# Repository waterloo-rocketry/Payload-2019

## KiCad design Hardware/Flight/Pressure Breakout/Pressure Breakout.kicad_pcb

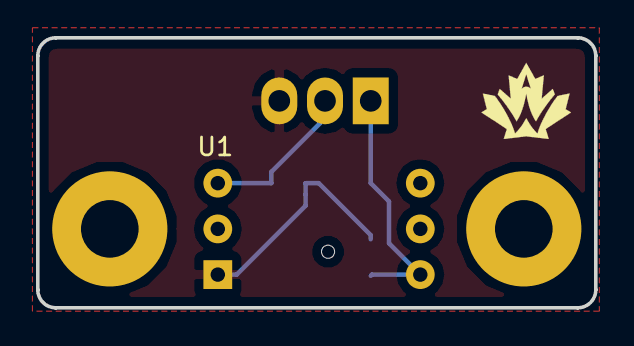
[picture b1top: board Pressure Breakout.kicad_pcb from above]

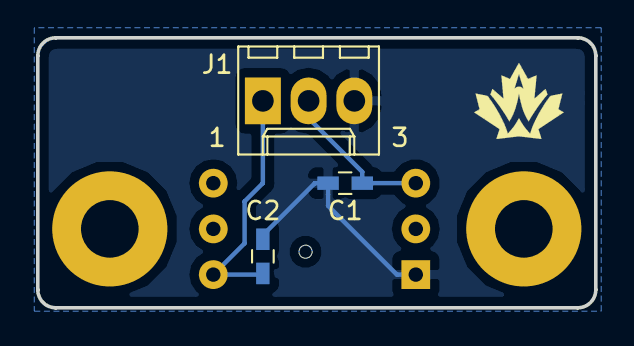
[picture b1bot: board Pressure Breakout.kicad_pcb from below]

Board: 2 copper layers, 31.0 x 15.0 mm, 4 parts (3 on the bottom side), 3 nets.

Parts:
C1: 0.001uF; C_0603_HandSoldering
C2: 0.1uF; C_0603_HandSoldering
J1: Conn_01x03; Molex_KK-6410-03_03x2.54mm_Straight
U1: ABPDANT005PGAA5; DIP-6_W11.25mm

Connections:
+5V: C2.1, J1.1, U1.6
/VOUT: C1.1, J1.2, U1.3
GND: C1.2, C2.2, J1.3, U1.1

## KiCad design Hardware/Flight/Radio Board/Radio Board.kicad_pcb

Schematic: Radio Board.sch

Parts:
C1, C2: 10uF; C_0603_HandSoldering
D1, D2, D3, D4: LED; LED_0603_HandSoldering
J1: Bus_Connector; Pin_Header_Straight_2x10_Pitch2.54mm
J2, J3: Conn_Coaxial; U.FL_Hirose_U.FL-R-SMT-1_Vertical
R1, R2: 10k; R_0603_HandSoldering
R3, R4: DNP; R_0603_HandSoldering
R5, R6, R7, R8: 70; R_0603_HandSoldering
U1, U2: RFM95W-915S2; Hopref_RFM9XW_SMD

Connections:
+3V3: C1.1, C2.1, J1.19, R1.1, R2.1, R3.1, R4.1, U1.13 (3.3V), U2.13 (3.3V)
/INT1: J1.5, R5.2, U1.14 (DIO0)
/INT2: J1.4, R6.2, U2.14 (DIO0)
/MISO: J1.6, U1.2 (MISO), U2.2 (MISO)
/MOSI: J1.7, U1.3 (MOSI), U2.3 (MOSI)
/SCK: J1.8, U1.4 (SCK), U2.4 (SCK)
/~CS1: J1.9, R3.2, U1.5 (NSS)
/~CS2: J1.10, R4.2, U2.5 (NSS)
GND: C1.2, C2.2, D1.1, D2.1, D3.1, D4.1, J1.1, J2.2, J3.2, U1.1 (GND), U1.8 (GND), U1.10 (GND), U2.1 (GND), U2.8 (GND), U2.10 (GND)
unnamed: D1.2, R5.1
unnamed: D2.2, R6.1
unnamed: D3.2, R7.1
unnamed: D4.2, R8.1
unnamed: J2.1, U1.9 (ANT)
unnamed: J3.1, U2.9 (ANT)
unnamed: R1.2, U1.6 (RESET)
unnamed: R2.2, U2.6 (RESET)
unnamed: R7.2, U1.11 (DIO3)
unnamed: R8.2, U2.11 (DIO3)

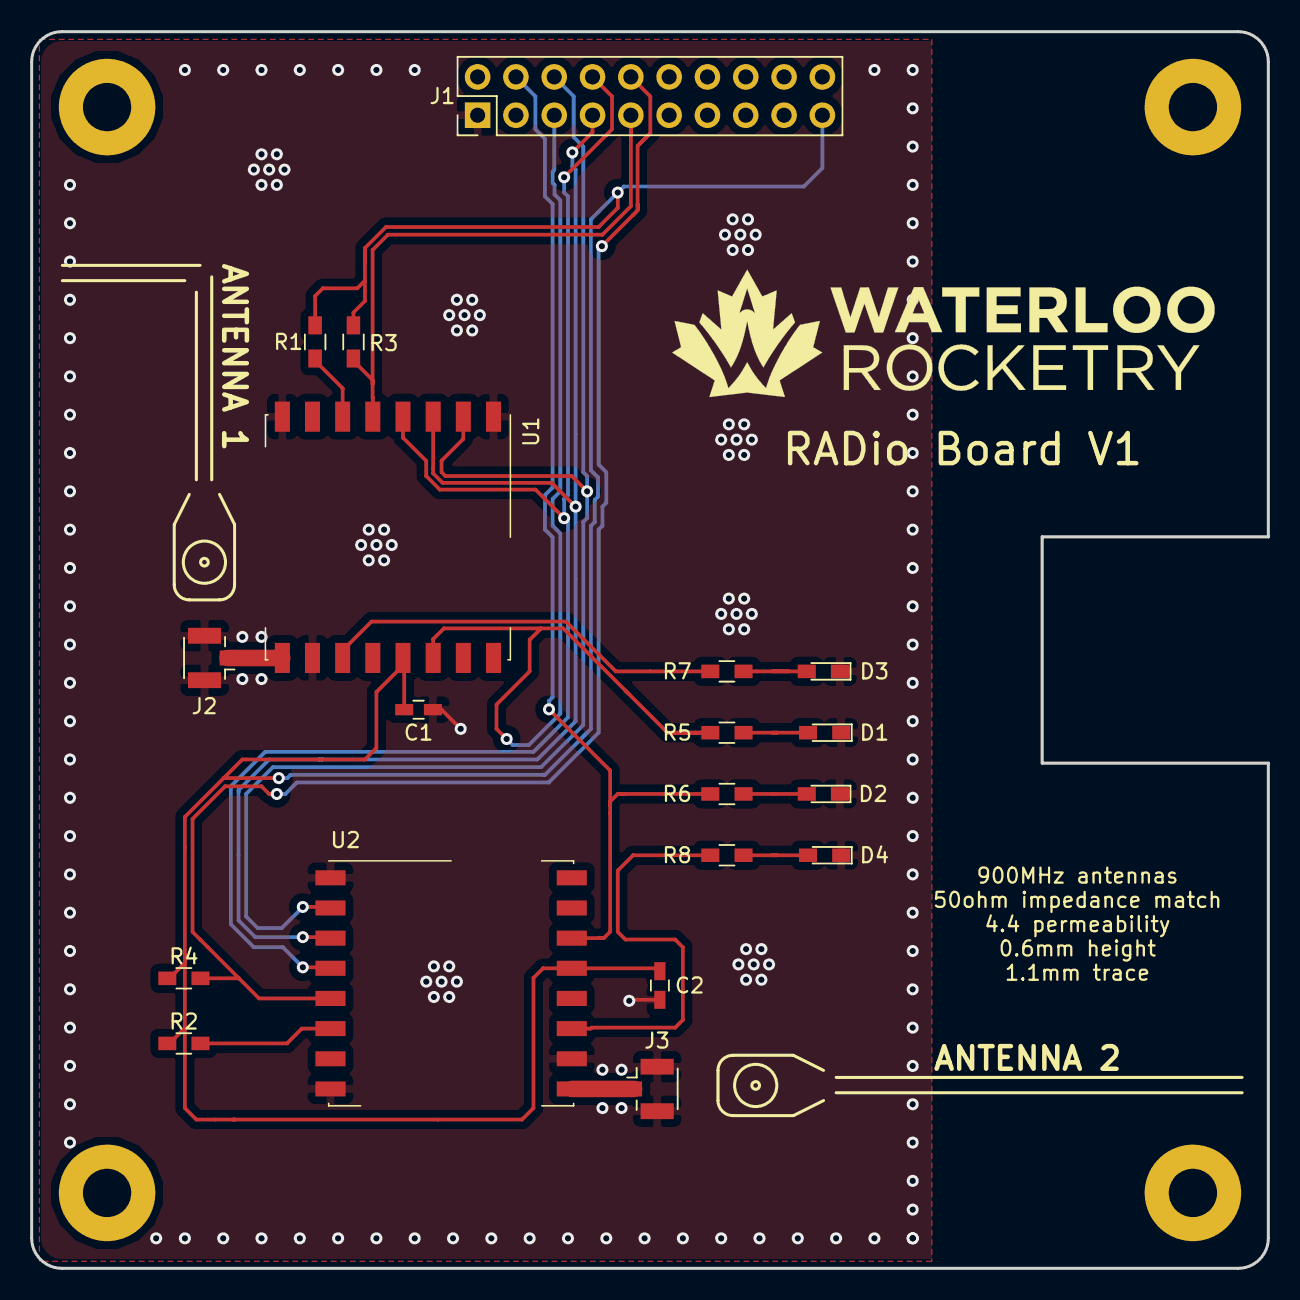
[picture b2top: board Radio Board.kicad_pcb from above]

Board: 2 copper layers, 82.0 x 82.0 mm, 19 parts (0 on the bottom side), 19 nets.

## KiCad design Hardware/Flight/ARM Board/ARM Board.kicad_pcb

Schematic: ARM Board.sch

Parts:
C1, C2: 47pF; C_0603_HandSoldering
C3: .01uF; C_0603_HandSoldering
C4, C5, C6, C22: 0.1uF; C_0603_HandSoldering
C7: 4.7uF; C_0603_HandSoldering
D1: D_TVS; D_0603
J1: Bus_Connector; Pin_Header_Straight_2x10_Pitch2.54mm
J2: USB_B_Micro; 10118194-0001LF
J3: Harwin_M80-5400642; connector_Harwin_M80-5000642
J4, J5: SD_Card; SD_Card_Receptacle
JP1, JP2, JP3, JP4, JP5, JP6, JP7, JP8, JP9, JP10, JP11, JP12, JP13, JP14, JP15, JP16, JP17, JP18, JP21, JP22, JP23, JP24, JP25, JP26, JP27, JP28, JP29, JP30: Jumper; SolderJumper-2_P1.3mm_Open_RoundedPad1.0x1.5mm
R1: DNP; R_0603_HandSoldering
R2, R3: 27; R_0603_HandSoldering
R4: R; R_0603_HandSoldering
U1: MCP2562-canhw; SOIC-8_3.9x4.9mm_Pitch1.27mm
U2: FT231XS; SSOP-20_3.9x8.7mm_P0.635mm
U6: MCP9700AT-ETT; SOT-23_Handsoldering

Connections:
+3V3: C6.1, C7.1, C22.1, J4.1, J4.4, J5.4, JP14.2, R4.1, U1.5, U6.1 (Vdd); also elsewhere on the board
+5V: C5.1, U1.3; also elsewhere on the board
/3V3_BUS: J1.19; also elsewhere on the board
/5_BUS: J1.20; also elsewhere on the board
/5_USB: C3.1, D1.1, J2.1, U2.15; also elsewhere on the board
/ARM&RAMMER/CANRX: JP9.1; also elsewhere on the board
/ARM&RAMMER/CANTX: JP8.2; also elsewhere on the board
/ARM&RAMMER/CARD_DETECT_1: J5.10; also elsewhere on the board
/ARM&RAMMER/CARD_DETECT_2: J4.10; also elsewhere on the board
/ARM&RAMMER/MISO1: JP17.1; also elsewhere on the board
/ARM&RAMMER/MISO2: JP5.2; also elsewhere on the board
/ARM&RAMMER/MOSI1: JP15.1; also elsewhere on the board
/ARM&RAMMER/MOSI2: JP4.2; also elsewhere on the board
/ARM&RAMMER/RADIO_INT_1: JP21.2; also elsewhere on the board
/ARM&RAMMER/RADIO_INT_2: JP22.2; also elsewhere on the board
/ARM&RAMMER/RES0: JP25.2; also elsewhere on the board
/ARM&RAMMER/RES1: JP26.2; also elsewhere on the board
/ARM&RAMMER/RES2: JP27.2; also elsewhere on the board
/ARM&RAMMER/RES3: JP28.2; also elsewhere on the board
/ARM&RAMMER/SCK1: JP16.1; also elsewhere on the board
/ARM&RAMMER/SCK2: JP3.2; also elsewhere on the board
/ARM&RAMMER/SCL: JP6.2; also elsewhere on the board
/ARM&RAMMER/SDA: JP7.2; also elsewhere on the board
/ARM&RAMMER/TEMP: U6.2 (Vout); also elsewhere on the board
/ARM&RAMMER/UART_RX: JP10.2, JP23.2; also elsewhere on the board
/ARM&RAMMER/UART_TX: JP11.2, JP24.2; also elsewhere on the board
/ARM&RAMMER/UART_~CTS: JP13.2; also elsewhere on the board
/ARM&RAMMER/UART_~RTS: JP12.2; also elsewhere on the board
/ARM&RAMMER/~CAN_EN: U1.8; also elsewhere on the board
/ARM&RAMMER/~CS1: JP14.1; also elsewhere on the board
/ARM&RAMMER/~CS1_2: JP18.1; also elsewhere on the board
/ARM&RAMMER/~CS2: JP2.2; also elsewhere on the board
/ARM&RAMMER/~CS2_2: JP1.2; also elsewhere on the board
/ARM&RAMMER/~FAULT1: JP29.2; also elsewhere on the board
/ARM&RAMMER/~FAULT2: JP30.2; also elsewhere on the board
/CAN-SENSE/VIN: J3.2; also elsewhere on the board
/D2+: R2.1, U2.11
/D2-: R3.1, U2.12
/D+: C1.1, J2.3, R2.2
/D-: C2.1, J2.2, R3.2
GND: C1.2, C2.2, C3.2, C4.2, C5.2, C6.2, C7.2, C22.2, D1.2, J1.1, J2.5, J3.3, J4.3, J4.6, J4.12, J4.13, J5.3, J5.6, J5.12, J5.13, U1.2, U2.6, U2.16, U6.3 (GND); also elsewhere on the board
unnamed: C4.1, U2.3, U2.13, U2.14
unnamed: J1.2, JP7.1
unnamed: J1.3, JP6.1
unnamed: J1.4, JP22.1
unnamed: J1.5, JP21.1
unnamed: J1.6, JP5.1
unnamed: J1.7, JP4.1
unnamed: J1.8, JP3.1
unnamed: J1.9, JP2.1
unnamed: J1.10, JP1.1
unnamed: J1.11, JP30.1
unnamed: J1.12, JP29.1
unnamed: J1.13, JP28.1
unnamed: J1.14, JP27.1
unnamed: J1.15, JP26.1
unnamed: J1.16, JP25.1
unnamed: J1.17, JP24.1
unnamed: J1.18, JP23.1
unnamed: J3.4, R1.1, U1.7
unnamed: J3.5, R1.2, U1.6
unnamed: J4.2, J5.2, JP15.2
unnamed: J4.5, J5.5, JP16.2
unnamed: J4.7, J5.7, JP17.2, R4.2
unnamed: J5.1, JP18.2
unnamed: JP8.1, U1.1
unnamed: JP9.2, U1.4
unnamed: JP10.1, U2.20
unnamed: JP11.1, U2.4
unnamed: JP12.1, U2.2
unnamed: JP13.1, U2.9

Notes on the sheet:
SD Card Logging
USB POWER + PROGRAMMING
CUBESAT BUS CONNECTOR
CAN LOGIC
POWER MANAGEMENT
ONLY POWERED WHEN USB CONNECTED
CANHW CURRENT SENSING

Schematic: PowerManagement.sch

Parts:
C8, C9: 10uF; C_0603_HandSoldering
D2, D3, D5: D_Schottky_x2_KCom_AAK; SOT-23_Handsoldering
D4: BAT60JFILM; D_SOD-323_HandSoldering
JP19, JP20: Jumper; SolderJumper-2_P1.3mm_Open_RoundedPad1.0x1.5mm
Q1: Q_PMOS_GSD; SOT-23_Handsoldering
R5: 10k; R_0603_HandSoldering
VR1: LD39200PU33R; DFN-6-1EP_3x3mm_Pitch0.95mm

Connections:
+3V3: D5.3; also elsewhere on the board
+5V: C8.1, D3.3, JP20.1, VR1.5, VR1.6; also elsewhere on the board
/3V3_BUS: D5.1; also elsewhere on the board
/5_BUS: D2.2, D3.1; also elsewhere on the board
/5_CANHW: Q1.2; also elsewhere on the board
/5_USB: D2.1, D3.2; also elsewhere on the board
GND: C8.2, C9.2, R5.2, VR1.3; also elsewhere on the board
unnamed: C9.1, D5.2, VR1.1, VR1.2
unnamed: D2.3, JP19.1
unnamed: D4.1, Q1.3
unnamed: D4.2, JP20.2
unnamed: JP19.2, Q1.1, R5.1

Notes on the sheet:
3.3v source selection (batt board or local)
5v source selection (canhw, bus or usb)
selected 5v source to 3.3v

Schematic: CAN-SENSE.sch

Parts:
C21: C
D6: D_TVS
R9: 62m
U5: INA180

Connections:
+3V3: C21.2, U5.5; also elsewhere on the board
/5_CANHW: R9.1, U5.4; also elsewhere on the board
/ARM&RAMMER/CURR_AMP: U5.1; also elsewhere on the board
/CAN-SENSE/VIN: D6.1; also elsewhere on the board
GND: C21.1, D6.2, U5.2; also elsewhere on the board
unnamed 66: R9.2, U5.3; also elsewhere on the board

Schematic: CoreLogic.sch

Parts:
C10: 4.7uF; C_0603_HandSoldering
C11, C12, C13, C17: 100nF; C_0603_HandSoldering
C14, C15: 1uF; C_0603_HandSoldering
C16: 10uF; C_0603_HandSoldering
C18: 0.1uF; C_0603_HandSoldering
C19, C20: C_Small; C_0603_HandSoldering
D7, D8, D9: LED; LED_0603_HandSoldering
J6: Conn_01x10; Pin_Header_Straight_2x05_Pitch2.54mm
JP31: Jumper; SolderJumper-2_P1.3mm_Open_RoundedPad1.0x1.5mm
L1: Ferrite_Bead; R_0603_HandSoldering
R6, R8: 4.7K; R_0603_HandSoldering
R10, R11, R12: 70; R_0603_HandSoldering
U3: STM32L4x6RxT6-symbols; STM32L4x6RxT6
U4: SRAM_23LC1024T-I_ST-ARMlib; TSSOP-8_4.4x3mm_Pitch0.65mm
Y1: Crystal; Crystal_HC49-U_Vertical

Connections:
+3V3: C10.1, C11.1, C12.1, C13.1, D7.2, D8.2, D9.2, J6.1, J6.7, L1.2, R6.1, R8.1, U3.1, U3.19, U3.32, U3.48, U3.64, U4.7, U4.8; also elsewhere on the board
/ARM&RAMMER/CANRX: U3.44; also elsewhere on the board
/ARM&RAMMER/CANTX: U3.45; also elsewhere on the board
/ARM&RAMMER/CARD_DETECT_1: U3.26; also elsewhere on the board
/ARM&RAMMER/CARD_DETECT_2: U3.27; also elsewhere on the board
/ARM&RAMMER/CURR_AMP: U3.10; also elsewhere on the board
/ARM&RAMMER/JTCK_SWCLK: J6.4, U3.49
/ARM&RAMMER/JTDI: J6.8, U3.50
/ARM&RAMMER/JTDO_SWO: J6.6, U3.55
/ARM&RAMMER/JTMS_SWDIO: J6.2, U3.46
/ARM&RAMMER/MISO1: U3.22; also elsewhere on the board
/ARM&RAMMER/MISO2: U3.35; also elsewhere on the board
/ARM&RAMMER/MISO3: U3.52, U4.2
/ARM&RAMMER/MOSI1: U3.23; also elsewhere on the board
/ARM&RAMMER/MOSI2: U3.36; also elsewhere on the board
/ARM&RAMMER/MOSI3: U3.53, U4.5
/ARM&RAMMER/PH3-BOOT0: J6.9, U3.60
/ARM&RAMMER/RADIO_INT_1: U3.11; also elsewhere on the board
/ARM&RAMMER/RADIO_INT_2: U3.25; also elsewhere on the board
/ARM&RAMMER/RES0: U3.37; also elsewhere on the board
/ARM&RAMMER/RES1: U3.38; also elsewhere on the board
/ARM&RAMMER/RES2: U3.39; also elsewhere on the board
/ARM&RAMMER/RES3: U3.40; also elsewhere on the board
/ARM&RAMMER/SCK1: U3.21; also elsewhere on the board
/ARM&RAMMER/SCK2: U3.42; also elsewhere on the board
/ARM&RAMMER/SCK3: U3.51, U4.6
/ARM&RAMMER/SCL: R6.2, U3.8; also elsewhere on the board
/ARM&RAMMER/SDA: R8.2, U3.9; also elsewhere on the board
/ARM&RAMMER/TEMP: U3.28; also elsewhere on the board
/ARM&RAMMER/UART_RX: U3.17; also elsewhere on the board
/ARM&RAMMER/UART_TX: U3.16; also elsewhere on the board
/ARM&RAMMER/UART_~CTS: U3.14; also elsewhere on the board
/ARM&RAMMER/UART_~RTS: U3.15; also elsewhere on the board
/ARM&RAMMER/~(JTRST|RST): J6.10, JP31.1, U3.56
/ARM&RAMMER/~CAN_EN: U3.43; also elsewhere on the board
/ARM&RAMMER/~CS1: U3.20; also elsewhere on the board
/ARM&RAMMER/~CS1_2: U3.24; also elsewhere on the board
/ARM&RAMMER/~CS2: U3.41; also elsewhere on the board
/ARM&RAMMER/~CS2_2: U3.34; also elsewhere on the board
/ARM&RAMMER/~CS3: U3.58, U4.1
/ARM&RAMMER/~FAULT1: U3.2; also elsewhere on the board
/ARM&RAMMER/~FAULT2: U3.54; also elsewhere on the board
/ARM&RAMMER/~HOLD3: U3.57
GND: C10.2, C11.2, C12.2, C13.2, C14.2, C15.2, C16.2, C17.2, C18.2, C19.2, C20.2, J6.3, J6.5, U3.12, U3.18, U3.31, U3.47, U3.63, U4.3, U4.4; also elsewhere on the board
unnamed: C14.1, C15.1, C16.1, C17.1, L1.1, U3.13
unnamed: C18.1, JP31.2, U3.7
unnamed: C19.1, U3.3, Y1.1
unnamed: C20.1, U3.4, Y1.2
unnamed: D7.1, R10.1
unnamed: D8.1, R11.1
unnamed: D9.1, R12.1
unnamed: R10.2, U3.59
unnamed: R11.2, U3.61
unnamed: R12.2, U3.62

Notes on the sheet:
RAM
STM PROGRAMMING HEADER
STM POWER MANAGEMENT
STM LOGIC
2v drop, 20mA max per pin

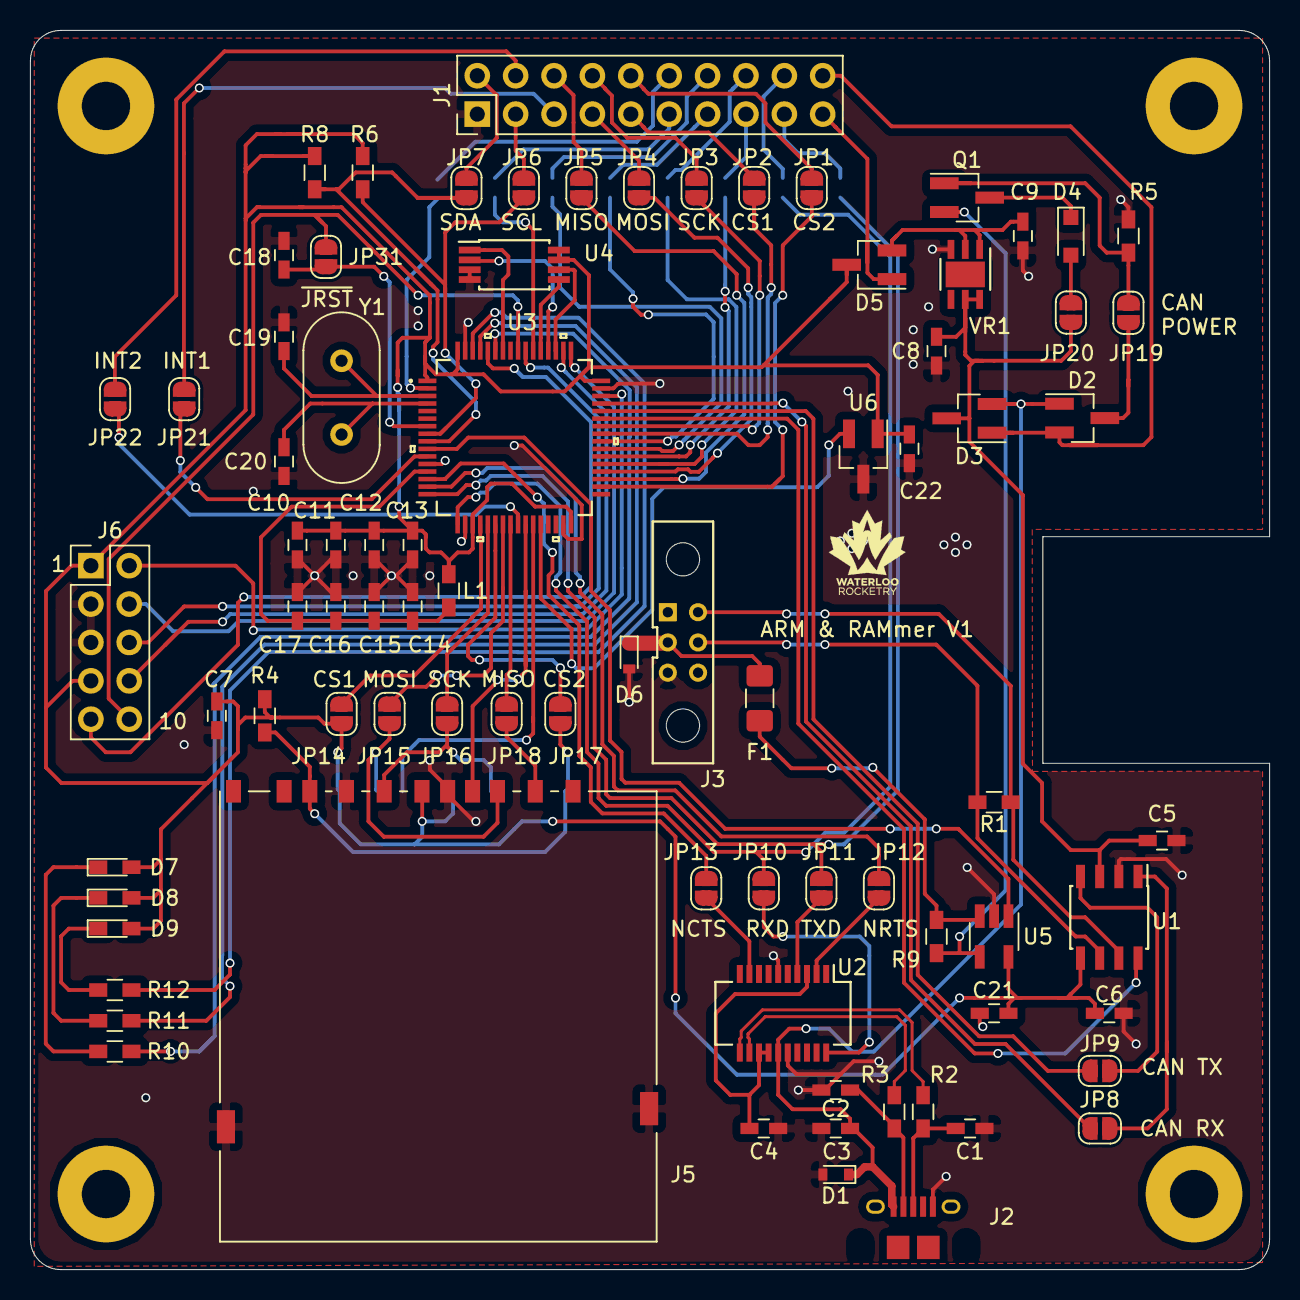
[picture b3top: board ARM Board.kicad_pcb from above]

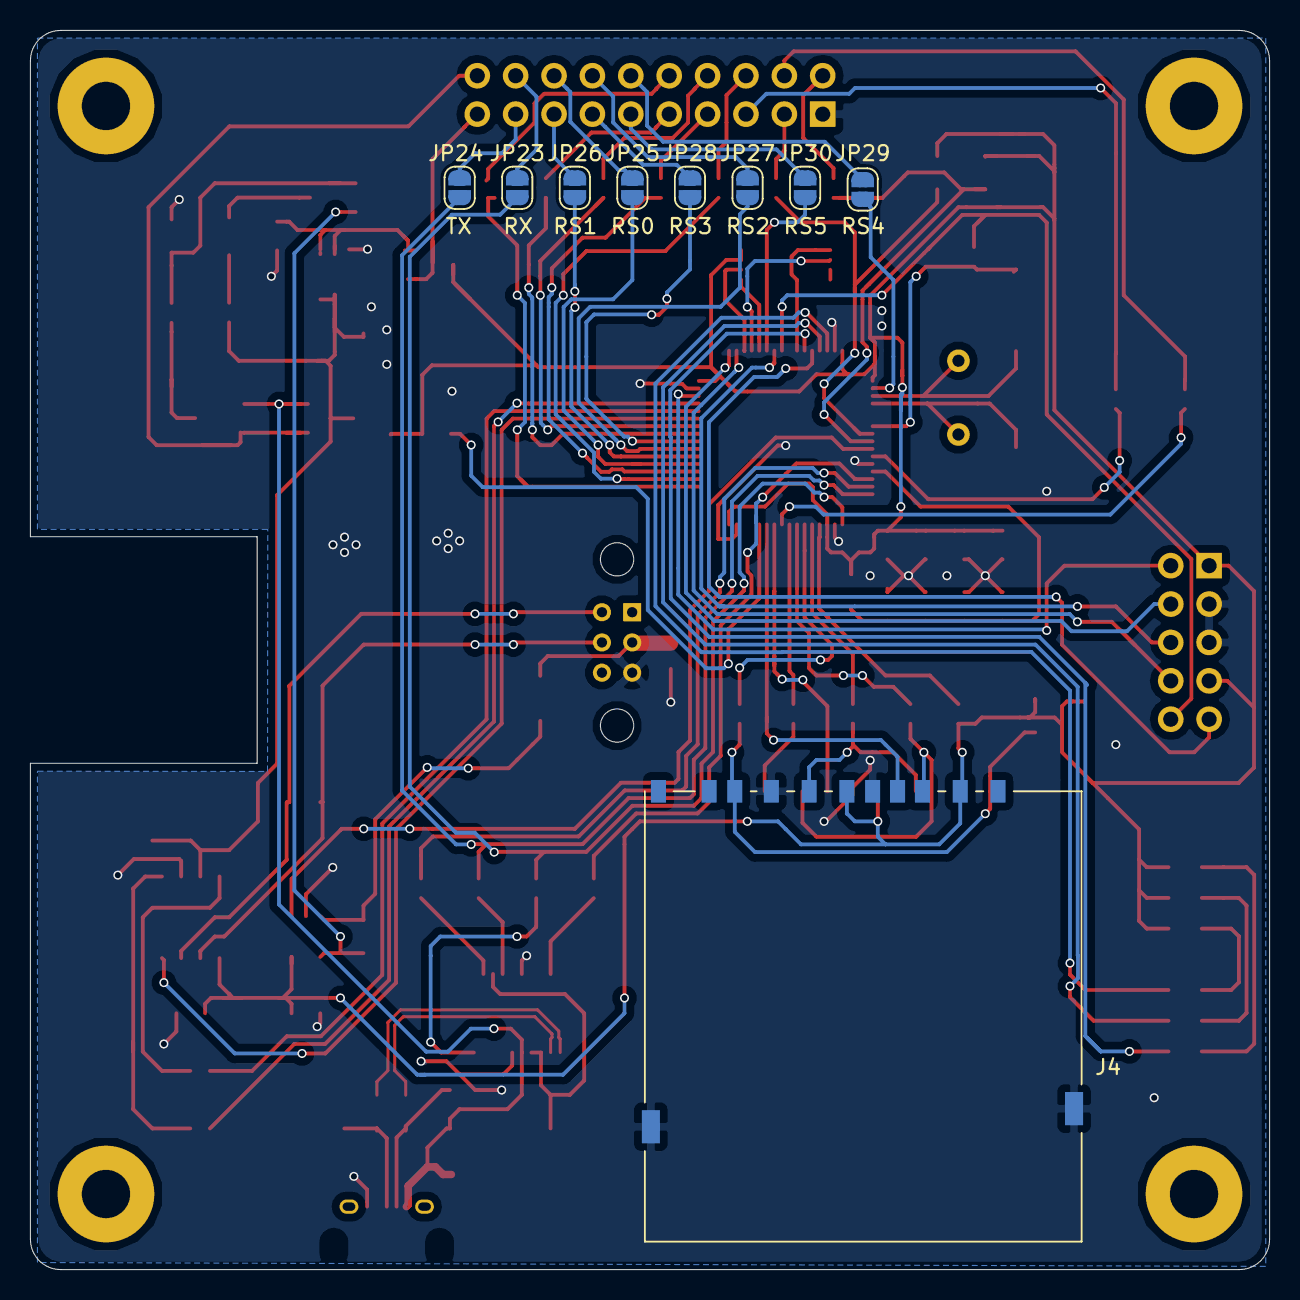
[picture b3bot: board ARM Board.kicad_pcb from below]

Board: 2 copper layers, 82.0 x 82.0 mm, 90 parts (9 on the bottom side), 99 nets.

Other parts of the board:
F1: Polyfuse; Fuse_1206_3216Metric_Pad1.42x1.75mm_HandSolder

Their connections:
/CAN-SENSE/VIN: F1.2; also elsewhere on the board
unnamed 66: F1.1; also elsewhere on the board

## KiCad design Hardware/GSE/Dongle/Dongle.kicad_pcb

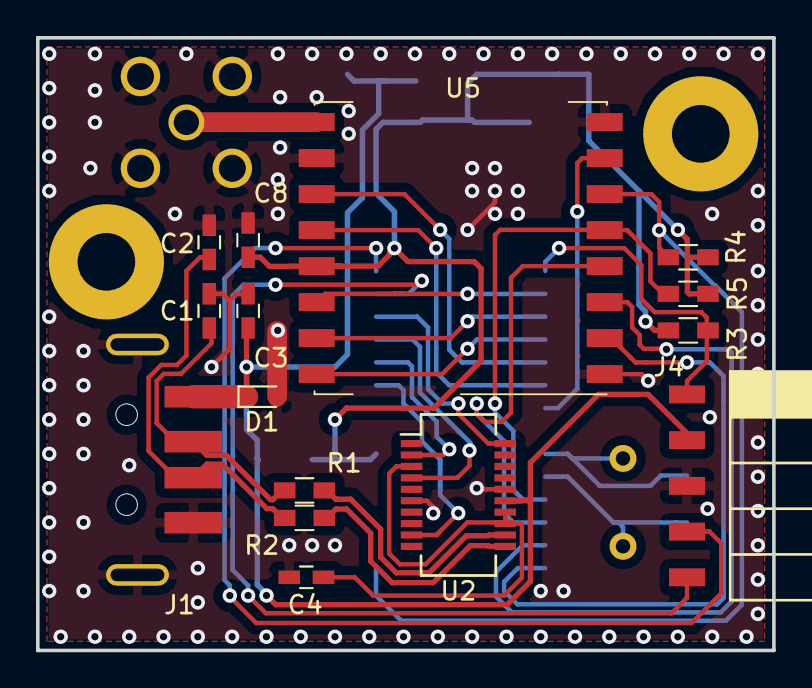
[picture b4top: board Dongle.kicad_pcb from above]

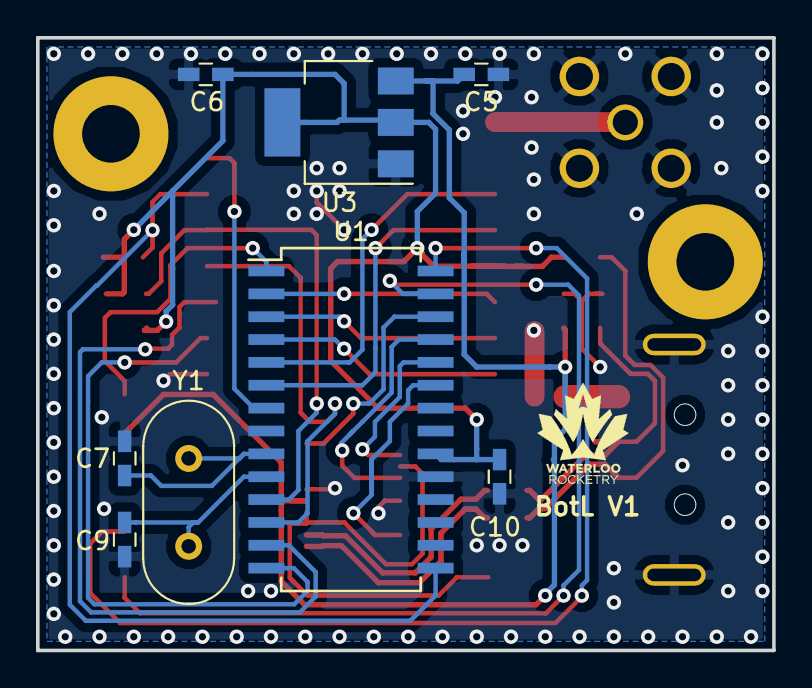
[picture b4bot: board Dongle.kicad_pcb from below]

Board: 2 copper layers, 40.9 x 34.0 mm, 24 parts (8 on the bottom side), 29 nets.

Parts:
C1, C2: 47pF; C_0603_HandSoldering
C3: 0.01uF; C_0603_HandSoldering
C4, C10: 0.1uF; C_0603_HandSoldering
C5, C6: 4.7uF; C_0603_HandSoldering
C7, C9: C; C_0603_HandSoldering
C8: 10uF; C_0603_HandSoldering
D1: D_TVS; D_0603
J1: USB_A; 629104151021
J2: Conn_Coaxial; CONSMA002
J4: Conn_01x05_Female; PinHeader_5x2.54_SMD_90deg_952-3198-1-ND
R1, R2: 27; R_0603_HandSoldering
R3, R4, R5: 10k; R_0603_HandSoldering
U1: PICLF26K83; SOIC-28W_7.5x18.7mm_Pitch1.27mm
U2: FT231XS; SSOP-20_3.9x8.7mm_P0.635mm
U3: AP2114H-3.3TRG1; SOT-223
U5: RFM95W-915S2; Hopref_RFM9XW_SMD
Y1: Crystal; Crystal_HC49-U_Vertical

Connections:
+3V3: C6.1, C8.1, C10.2, R3.1, R4.1, R5.1, U1.20, U3.2, U3.4, U5.13
+5V: C3.1, C5.1, D1.1, J1.1, J4.2, U2.15, U3.3
/CS: R5.2, U1.11, U5.5
/CTS: U1.23, U2.9
/D1+: C2.1, J1.3, R2.2
/D1-: C1.1, J1.2, R1.2
/DIN: U1.26, U2.20
/DIO0: U1.2, U5.14
/DIO1: U1.3, U5.15
/DIO2: U1.4, U5.16
/DIO3: U1.5, U5.11
/DIO4: U1.6, U5.12
/DIO5: U1.7, U5.7
/DOUT: U1.25, U2.4
/ICSPCLK: J4.5, U1.27
/ICSPDAT: J4.4, U1.28
/MISO: U1.14, U5.2
/MOSI: U1.13, U5.3
/OSC1: C7.1, U1.9, Y1.1
/OSC2: C9.1, U1.10, Y1.2
/RESET: R4.2, U1.15, U5.6
/RTS: U1.24, U2.2
/SCK: U1.12, U5.4
/USBD+: R2.1, U2.11
/USBD-: R1.1, U2.12
/~MCLR: J4.1, R3.2, U1.1
GND: C1.2, C2.2, C3.2, C4.2, C5.2, C6.2, C7.2, C8.2, C9.2, C10.1, D1.2, J1.4, J1.5, J2.2, J4.3, U1.8, U1.19, U2.6, U2.16, U3.1, U5.1, U5.8, U5.10
unnamed: C4.1, U2.3, U2.13, U2.14
unnamed: J2.1, U5.9

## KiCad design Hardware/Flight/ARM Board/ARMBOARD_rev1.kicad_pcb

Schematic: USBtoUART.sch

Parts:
C15, C16: 47pF; C_0603
C17: 100nF; C_0603
FB1: Ferrite_Bead; C_0603
R9, R10, R11, R12: 10K; R_0603
R13, R14: 27; R_0603
U5: FT230XS; SSOP-16_3.9x4.9mm_Pitch0.635mm

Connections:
/D+: C16.1, R14.2; also elsewhere on the board
/D-: C15.1, R13.2; also elsewhere on the board
/USBtoUART/USBD+: R14.1, U5.8
/USBtoUART/USBD-: R13.1, U5.9
/USBtoUART/USB_5V: FB1.2; also elsewhere on the board
GND: C15.2, C16.2, C17.2, U5.5, U5.13; also elsewhere on the board
UART_RX: R9.1, U5.1; also elsewhere on the board
UART_TX: R10.1, U5.4; also elsewhere on the board
UART_~CTS: R12.1, U5.6; also elsewhere on the board
UART_~RTS: R11.1, U5.2; also elsewhere on the board
VBUS: FB1.1, U5.12; also elsewhere on the board
VCCIO: C17.1, R9.2, R10.2, R11.2, R12.2, U5.3, U5.10, U5.11

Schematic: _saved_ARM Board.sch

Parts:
C1, C2: C_Small; C_0603
C3, C5: 4.7uF; C_0603
C4, C6, C12, C13, C14: 100nF; C_0603
C7, C8, C10: 10uF; C_0603
C9: 1uF; C_0603
C11: 100uF; C_0805
D1, D2: BAT60JFILM; D_SOD-323_HandSoldering
J1: USB_OTG; USB_Micro-B_Amphenol_10118193-0001LF
J2: Conn_01x10; Pin_Header_Straight_2x05_Pitch2.54mm
J3, J6: SD_WM6698CT-ND; MICROSD_WM6698CT-ND
J4: Conn_01x20_Female; Pin_Header_Straight_2x10_Pitch2.54mm
J5: Harwin_M80-5400642; connector_Harwin_M80-5000642
J7: 1053131202; MOLEX_1053131202
L1: Ferrite_Bead; R_0603_HandSoldering
R1, R8, R15, R16: DNP; R_0603
R2: 0; R_0603
R3: 10K; R_0603
R5: 120; R_0603
R6, R7: 4.7K; R_0603
U2: STM32L4x6RxT6
U3: SRAM_23LC1024T-I_ST; TSSOP-8_4.4x3mm_Pitch0.65mm
U4: MCP2562; SOIC-8_3.9x4.9mm_Pitch1.27mm
VR1: LD39200PU33R; DFN-6-1EP_3x3mm_Pitch0.95mm
Y1: Crystal_GND23; MC-306

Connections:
/D+: J1.3; also elsewhere on the board
/D-: J1.2; also elsewhere on the board
/USBtoUART/USB_5V: J1.1; also elsewhere on the board
CANRX: U2.44, U4.4
CANTX: U2.45, U4.1
GND: C1.2, C2.2, C3.2, C4.2, C5.2, C6.2, C7.2, C8.2, C9.2, C10.2, C11.2, C12.2, C13.2, C14.2, J1.5, J1.6, J2.3, J2.5, J3.6, J3.G1, J3.G2, J3.G3, J3.G4, J4.1, J5.3, J6.6, J6.G1, J6.G2, J6.G3, J6.G4, R15.2, R16.2, U2.12, U2.18, U2.31, U2.47, U2.63, U3.3, U3.4, U4.2, VR1.3, VR1.7; also elsewhere on the board
JTCK_SWCLK: J2.4, U2.49
JTDI: J2.8, U2.50
JTDO_SWO: J2.6, U2.55
JTMS_SWDIO: J2.2, U2.46
JTRST: J2.10, R2.1, U2.56
MISO1: U2.22, U3.2
MISO2: J4.6, U2.35
MISO3: J3.7, J6.7, R1.2, R8.2, U2.52
MOSI1: U2.23, U3.5
MOSI2: J4.7, U2.36
MOSI3: J3.3, J6.3, U2.53
unnamed: C1.1, U2.3, Y1.1
unnamed: C2.1, U2.4, Y1.4
unnamed: C9.1, C10.1, C11.1, L1.1, U2.13
unnamed: D1.2, D2.2, J7.2
unnamed: J5.2, U4.3
unnamed: J5.4, R5.1, U4.7
unnamed: J5.5, R5.2, U4.6
unnamed: R2.2, R3.2, U2.7
unnamed: R15.1, Y1.2
unnamed: R16.1, Y1.3
SCK1: U2.21, U3.6
SCK2: J4.8, U2.42
SCK3: J3.5, J6.5, U2.51
SCL: J4.3, R6.2, U2.8
SDA: J4.2, R7.2, U2.9
UART_RX: U2.24; also elsewhere on the board
UART_TX: U2.25; also elsewhere on the board
UART_~CTS: U2.34; also elsewhere on the board
UART_~RTS: U2.27; also elsewhere on the board
VBUS: C5.1, C6.1, C7.1, VR1.5, VR1.6; also elsewhere on the board
VDD33: C3.1, C4.1, C12.1, C13.1, C14.1, J2.1, J3.4, J6.4, J7.1, L1.2, R1.1, R3.1, R6.1, R7.1, R8.1, U2.1, U2.19, U2.32, U2.48, U2.64, U3.8, U4.5
VDD33_IN: D2.1, J4.19
VDD33_USB: C8.1, D1.1, VR1.1, VR1.2
~CAN_EN: U2.43, U4.8
~CS1: U2.26, U3.1
~CS2: J4.9, U2.33
~CS2_2: J4.10, U2.30
~CS3: J6.2, U2.39
~CS3_2: J3.2, U2.40
~HOLD1: U2.20, U3.7

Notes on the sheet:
USB to Basic UART
SD Card Logging
RAM

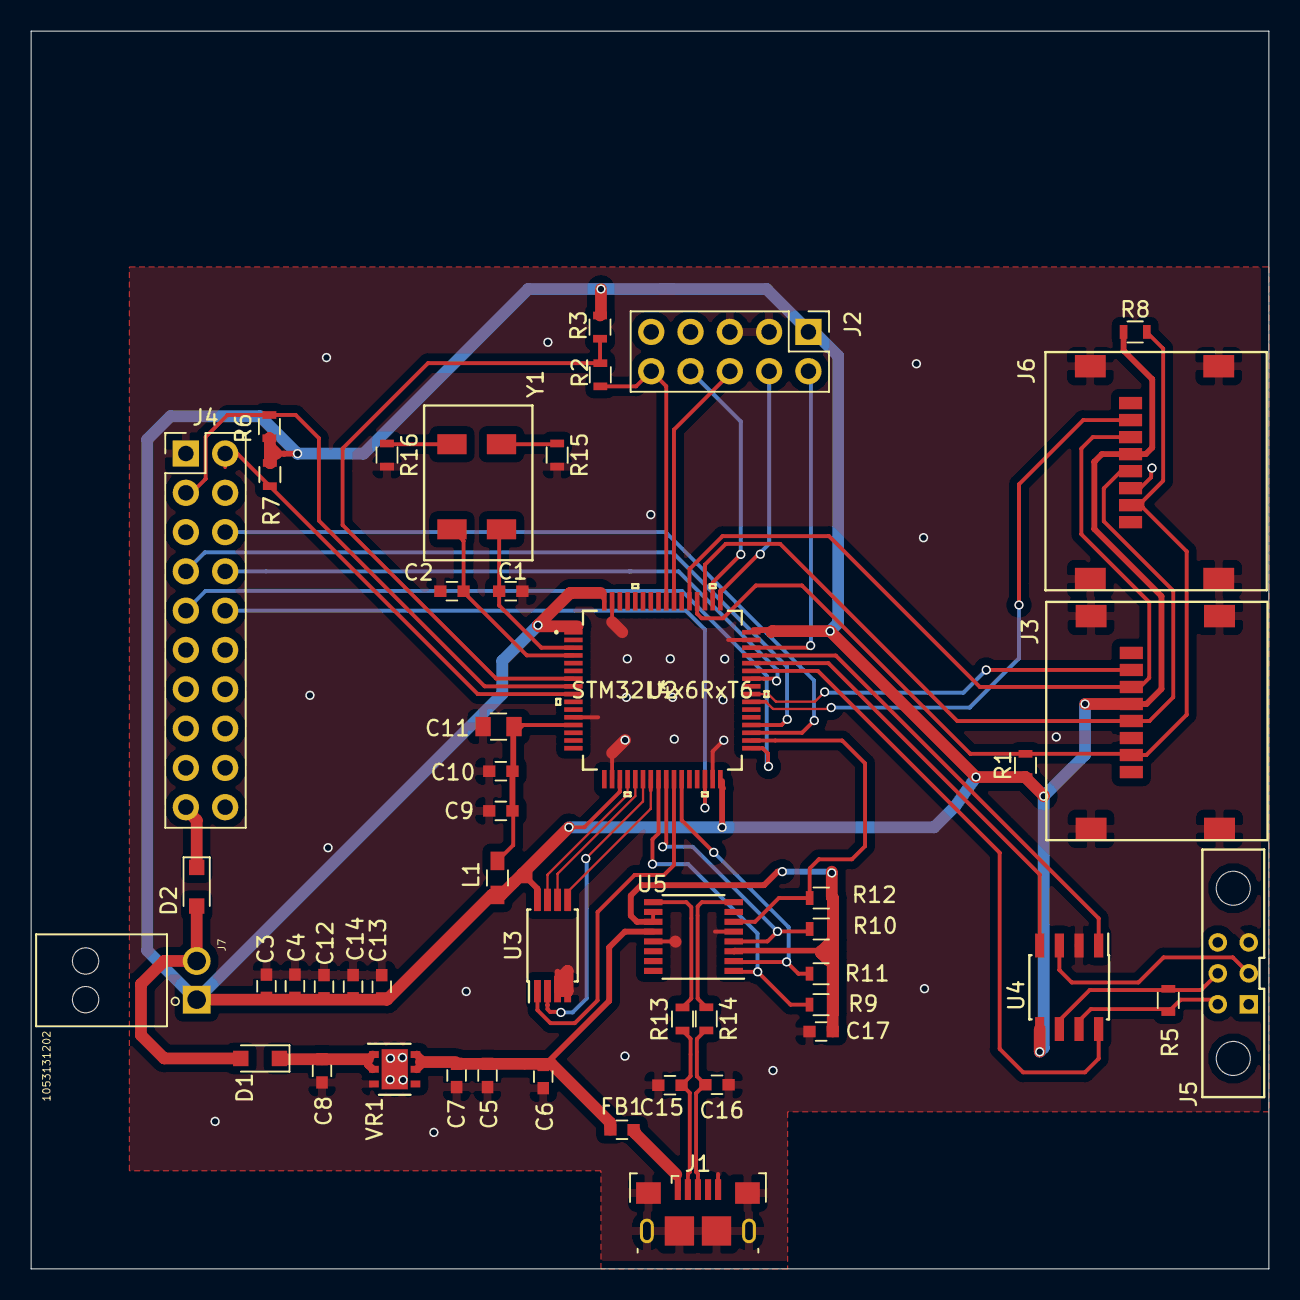
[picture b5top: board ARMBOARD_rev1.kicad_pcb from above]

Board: 2 copper layers, 80.0 x 80.0 mm, 49 parts (0 on the bottom side), 50 nets.

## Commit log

2018-11-01 updated layout
2018-11-07 Init
    Initialization of ARM board project files
2018-11-07 Updated STM footprint
    Linked sch and footprint
2018-11-09 Added footprint and sch for SD logger, pull up resistor on data out as per documentation found in Datasheets and Documentation folder
2018-11-12 Added footprint and sch for IO connector and USB
2018-11-23 Added crystal, caps and MsP430
2018-11-24 added schematic for dongle board
2018-11-26 power supply for stm32
2018-11-28 Minor changes to cap values
2018-11-28 Added USB to UART and connected XTAL
2018-11-28 Completion of previous commit
2018-11-28 Battery Management code and text files upload
2018-11-29 RAM and cleanup
    Added RAM module, seperate sch for USB to UART, SPI pin net flags
2018-11-29 dongle netlist
2018-12-01 prelim dongle routing
2018-12-01 Added SPI connections to STM
2018-12-02 GSE dongle layout
2018-12-07 Added regulator, CAN bus and power switch
2018-12-15 new connectors for GSE board
2018-12-15 rearranged libraries
2018-12-15 radio board
2018-12-15 radio board int resets and antenna
2018-12-18 Added JTAG I/O, USB UART connections, modified headers and power circuit, added I2C for MSP430
2018-12-20 Updated libraries and footprints, netlist
2018-12-20 Radio board layout
2019-01-07 SPI added to header, Layout finished
2019-01-07 fixed library conflicts
2019-01-10 starting rev2 of board layout
2019-01-11 Started new layout rev 2
2019-01-12 STM part updated
2019-01-12 finished layout rev2 on ARM board
2019-01-28 updated dongle for LoRa
2019-02-05 new dongle with LoRa for review
2019-03-05 updated dongle based on review
2019-03-11 ARM board refactor
2019-03-11 updated ARM board schematic with updates specified on slack
2019-03-12 Jumpers for ARM board added
2019-03-13 addressed review comments from Alex
2019-03-19 Jun's txt file
2019-03-20 ARM board: Added polyfuse Added lines for radio interrupt
2019-03-22 radio board for review
2019-03-22 forgot to save :wutface:
2019-03-22 silk screen mods and CAD generation for radio board
2019-03-27 Experiment board commit
2019-03-28 finished schematic for experiment board
2019-03-29 ARM review comments
2019-03-29 ARM board for review
2019-03-29 Radio Review
    Added Debug LEDs
    Rerouted traces to keep away from edge
    Made RF traces shorter
    Switched RFM95W to SMD version
2019-03-29 small routing mods
2019-03-30 added battery board + ADCs for experiment board
2019-03-30 osmdroid stuff
2019-04-02 connected GPIO to ARM board
2019-04-02 updated battery, experiment board. Added temp sensor to ARM board
2019-04-03 addressed Alex's ARM review comments
2019-04-04 addressing aarons comments for radio board
2019-04-04 radio gerbers
2019-04-05 fixed offline stuff not loading
2019-04-05 Radio board review fixes Spaced resistors away from LEDs Adjusted antenna trace Set solder mask clearance to 0
2019-04-06 fixed battery board comments
2019-04-08 swapped ADC package on experiment board
2019-04-11 fixed changes in experiment board
2019-05-06 Added support for Reading information from Serial. Note, that there is no support for writing to serial
2019-05-06 Develop UI and front end for GSE. Set up multithreading back-end in preperation with Dongle work.
2019-05-08 added map stuff
2019-05-11 updated pressure breakout
2019-05-23 Create 2_pin_sinwave.ino
    Original Arduino Code
2019-05-25 Adam V2
    A0 and A1 outputting pwm that is 90 degrees out of phase with each other, and A2 and A3 switching between 0 and 1 for the dir pins.
2019-05-30 Updated Working Code
2019-06-04 adding react native
2019-06-04 omg it works

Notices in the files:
parts and their libraries:
Copyright 2016 Accelerated Designs. All rights reserved.
